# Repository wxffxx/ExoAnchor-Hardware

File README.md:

# ExoAnchor Hardware

[中文](README_zh.md)

This repository contains ExoAnchor hardware design outputs and hardware-specific instructions. Firmware, system architecture, and board capability truth live in the main [ExoAnchor repository](https://github.com/wxffxx/ExoAnchor).

## Current contents

| Path | Role |
| --- | --- |
| [`ESP32P4/exoanchor-p4-v2.4a6/`](ESP32P4/exoanchor-p4-v2.4a6/) | Standalone JLCEDA and KiCad V2.4A6 projects; conversion checked, manufacturing signoff pending |
| [`ESP32P4/exoanchor-p4-v2.3b4/`](ESP32P4/exoanchor-p4-v2.3b4/) | Standalone four-layer V2.3B4 JLCEDA and KiCad projects; historical revision, conversion checked |
| [`ESP32P4/exoanchor-p4-v2.3b6/`](ESP32P4/exoanchor-p4-v2.3b6/) | Standalone six-layer V2.3B6 JLCEDA and KiCad projects; historical revision, conversion checked |
| [`ESP32P4/simple-diy/`](ESP32P4/simple-diy/) | Waveshare simple DIY designs and expansion board |
| [`ESP32P4/archive/`](ESP32P4/archive/) | Historical material no longer used by new designs |
| `assets/brand/` | Brand geometry for PCB silkscreen |
| `ArmLinux/CM4_CH552/`, `ESP32S31/` | Reserved platform directories, not delivered designs |

A directory, netlist, or production output does not imply validated or production-ready hardware. A capability requires an identified revision, firmware profile, and corresponding hardware evidence.

Chinese documentation is authoritative. English README files are synchronized
mirrors; resolve differences from `_zh.md`.

## License

Original ExoAnchor software, firmware and documentation are licensed under the
[MIT License](LICENSE). Original hardware designs use the same policy, including
permission to manufacture and sell hardware from covered design files.

Unless a file says otherwise, this license covers all original materials that
the ExoAnchor contributors have the right to license, including schematics,
PCB and CAD source projects, BOMs, netlists, mechanical models, manufacturing
materials, and project documentation. Copies or substantial portions must
retain the copyright and permission notice from `LICENSE`. Third-party products
and materials retain their own terms; the MIT License does not grant rights to
ExoAnchor trademarks or third-party material.

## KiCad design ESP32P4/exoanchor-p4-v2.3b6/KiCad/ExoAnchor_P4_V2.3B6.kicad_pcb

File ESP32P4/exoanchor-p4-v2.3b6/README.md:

# ExoAnchor P4 V2.3B6 standalone project

[中文](README_zh.md)

Prepared on 2026-10-22 from local archives. This directory extracts `ESP32P4_Prototype_V2.3b6layers_260724封存` with its schematics, PCB, and library dependencies. No current cloud-project synchronization was performed. Chinese documentation is authoritative.

The native source marks `Appendix` as deleted. Only eight active design pages are included. The original repository netlist dated 2026-07-26 is also retained under `reference/` for historical traceability, not as a newly generated manufacturing output.

## Open the projects

| Format | Entry point | Instructions |
| --- | --- | --- |
| Native JLCEDA archive | [ExoAnchor_P4_V2.3B6.epro2](JLCEDA/ExoAnchor_P4_V2.3B6.epro2) | Successfully imported and PCB opened in fully offline JLCEDA Pro V4.1.60 |
| Native JLCEDA folder project | [ExoAnchor_P4_V2.3B6.eprj3](JLCEDA/ExoAnchor_P4_V2.3B6/ExoAnchor_P4_V2.3B6.eprj3) | Generated by the native application; keep its `pcb/` and `sch/` directories |
| KiCad project | [ExoAnchor_P4_V2.3B6.kicad_pro](KiCad/ExoAnchor_P4_V2.3B6.kicad_pro) | Keep the complete `KiCad/` directory |
| KiCad schematic | [ExoAnchor_P4_V2.3B6.kicad_sch](KiCad/ExoAnchor_P4_V2.3B6.kicad_sch) | Navigation root and eight design sheets |
| KiCad PCB | [ExoAnchor_P4_V2.3B6.kicad_pcb](KiCad/ExoAnchor_P4_V2.3B6.kicad_pcb) | 6 copper layers with tracks, vias, and copper zones |

Conversion and checks used **KiCad Nightly 10.99.0-1556-g74ef325b2f**. Compatibility with stable KiCad 9/10 was not verified. Local symbols, 38 footprints, and `${KIPRJMOD}` library tables are included. Relocating only `KiCad/` to an unrelated temporary directory produced an identical fresh netlist. Source 3D references are retained, but STEP/WRL geometry is not bundled.

## Checks and repairs

| Item | Result |
| --- | --- |
| Design | One board; eight active sheets plus the KiCad navigation root |
| Sheets | P1, USB_UART/Other IO, ETH, P4, HDMI_Captrue_MS2109, Power, PCIe, TF |
| Components | 185 in source PCB, KiCad PCB, and schematic; identical reference sets |
| Pads | 753 checked; pad-number sets and net names match |
| Connectivity | 149 / 149 nonempty source net endpoint sets match |
| Placement | No component position difference above 1 micrometre after import translation |
| PCB | 6 copper layers, 1841 straight tracks, 25 arc tracks, 401 vias |
| Free pads | Five extra footprint containers; 190 footprint objects in total |
| Native extraction | 220 design/library/support documents retain source bytes; configuration changes the default PCB |

Reports: [conversion parity](validation/parity.json), [native verification](validation/native-source-verification.json), [native application check](validation/native-open.json), [relocation](validation/portability.json).

The KiCad conversion repairs SMD pads, 185 schematic/PCB component links, cross-sheet labels, source short-circuit symbols, power references, and local library defaults. It restores 16 independent native PCIe wire groups to correct V2 compatibility-export merging of GND, 3V3AUX, and WAKE#. `U12.B10` is 3V3AUX; `U12.B11` is WAKE#. Front/back R-shaped copper artwork is reconstructed from source paths with arcs sampled at a maximum step of 2 degrees. Source text, frames, and layouts remain, including existing frame overlaps.

All nonzero native V3 straight tracks have matching V2 compatibility-export records. Both variants omit four zero-length native line records. See [track comparison](validation/native-track-comparison.json). Cross-format geometry is not claimed to be byte-identical. Native JLCEDA design documents are unchanged.

## Outstanding signoff

This is an extraction and conversion delivery, not manufacturing approval.

- KiCad DRC: **1521 items**, comprising 1329 errors and 192 warnings; zero reported unconnected items, no reported `shorting_items` or `invalid_padstack`. Clearance, track/via dimensions, thermals, board edges, silkscreen, and other findings remain.
- KiCad ERC: **777 items**, including pin conflicts, undriven pins, library differences, and dangling endpoints. Rules were not disabled or waived to clear the reports.
- These checks use default/imported KiCad rules. Original JLCEDA rules and manufacturing stackup parameters have not been exhaustively mapped; findings need attribution to source design, rule differences, or residual conversion differences.
- Native JLCEDA ERC/DRC, fabrication, assembly, power-on, and interface testing were not performed here.

See [rules summary](validation/rules-summary.json), [DRC](validation/pcb-drc.json), and [ERC](validation/sch-erc.json).

## Contents and provenance

| Path | Contents |
| --- | --- |
| `JLCEDA/` | Native import archive and editable folder project |
| `KiCad/` | Project, schematics, PCB, local symbols and footprints |
| `preview/` | PCB SVG/PNG, schematic SVG pages and overview; browsing aids |
| `reference/` | Original V2 compatibility export with known PCIe issue and historical 2026-07-26 netlist |
| `validation/` | Provenance, hashes, conversion repairs, connectivity and rule reports |
| `scripts/` | Standalone conversion verification scripts |
| `SHA256SUMS.txt` | Delivered file hashes |

Native source: `hardware-reserve/lceda-2026-10-01/source/ProPrj_ExoAnchor-ESP32P4_2026-09-30.epro2`. Initial KiCad import source: `ProPrj_ExoAnchor-ESP32P4_2026-10-19.epro`, followed by native-evidence repairs. Source hashes and extraction scope are in `validation/extraction-v3.json` and `validation/extraction.json`. These paths are provenance only; the original workspace is not required to open this delivery.

**Do not use `reference/V2_compatibility_export_as_received.epro` as the current design entry point.** Use the native `.epro2` or `.eprj3` above. `LICENSE` is copied from the hardware repository's MIT license; third-party library identifiers and properties remain.

## Repeat the checks

From this directory with a compatible `kicad-cli`:

```sh
kicad-cli sch export netlist --format kicadxml -o validation/kicad-netlist.xml KiCad/ExoAnchor_P4_V2.3B6.kicad_sch
python3 scripts/verify_conversion.py
```

The script resolves its own project directory and exits nonzero on parity failure. It does not replace ERC/DRC, manufacturing review, or physical validation.

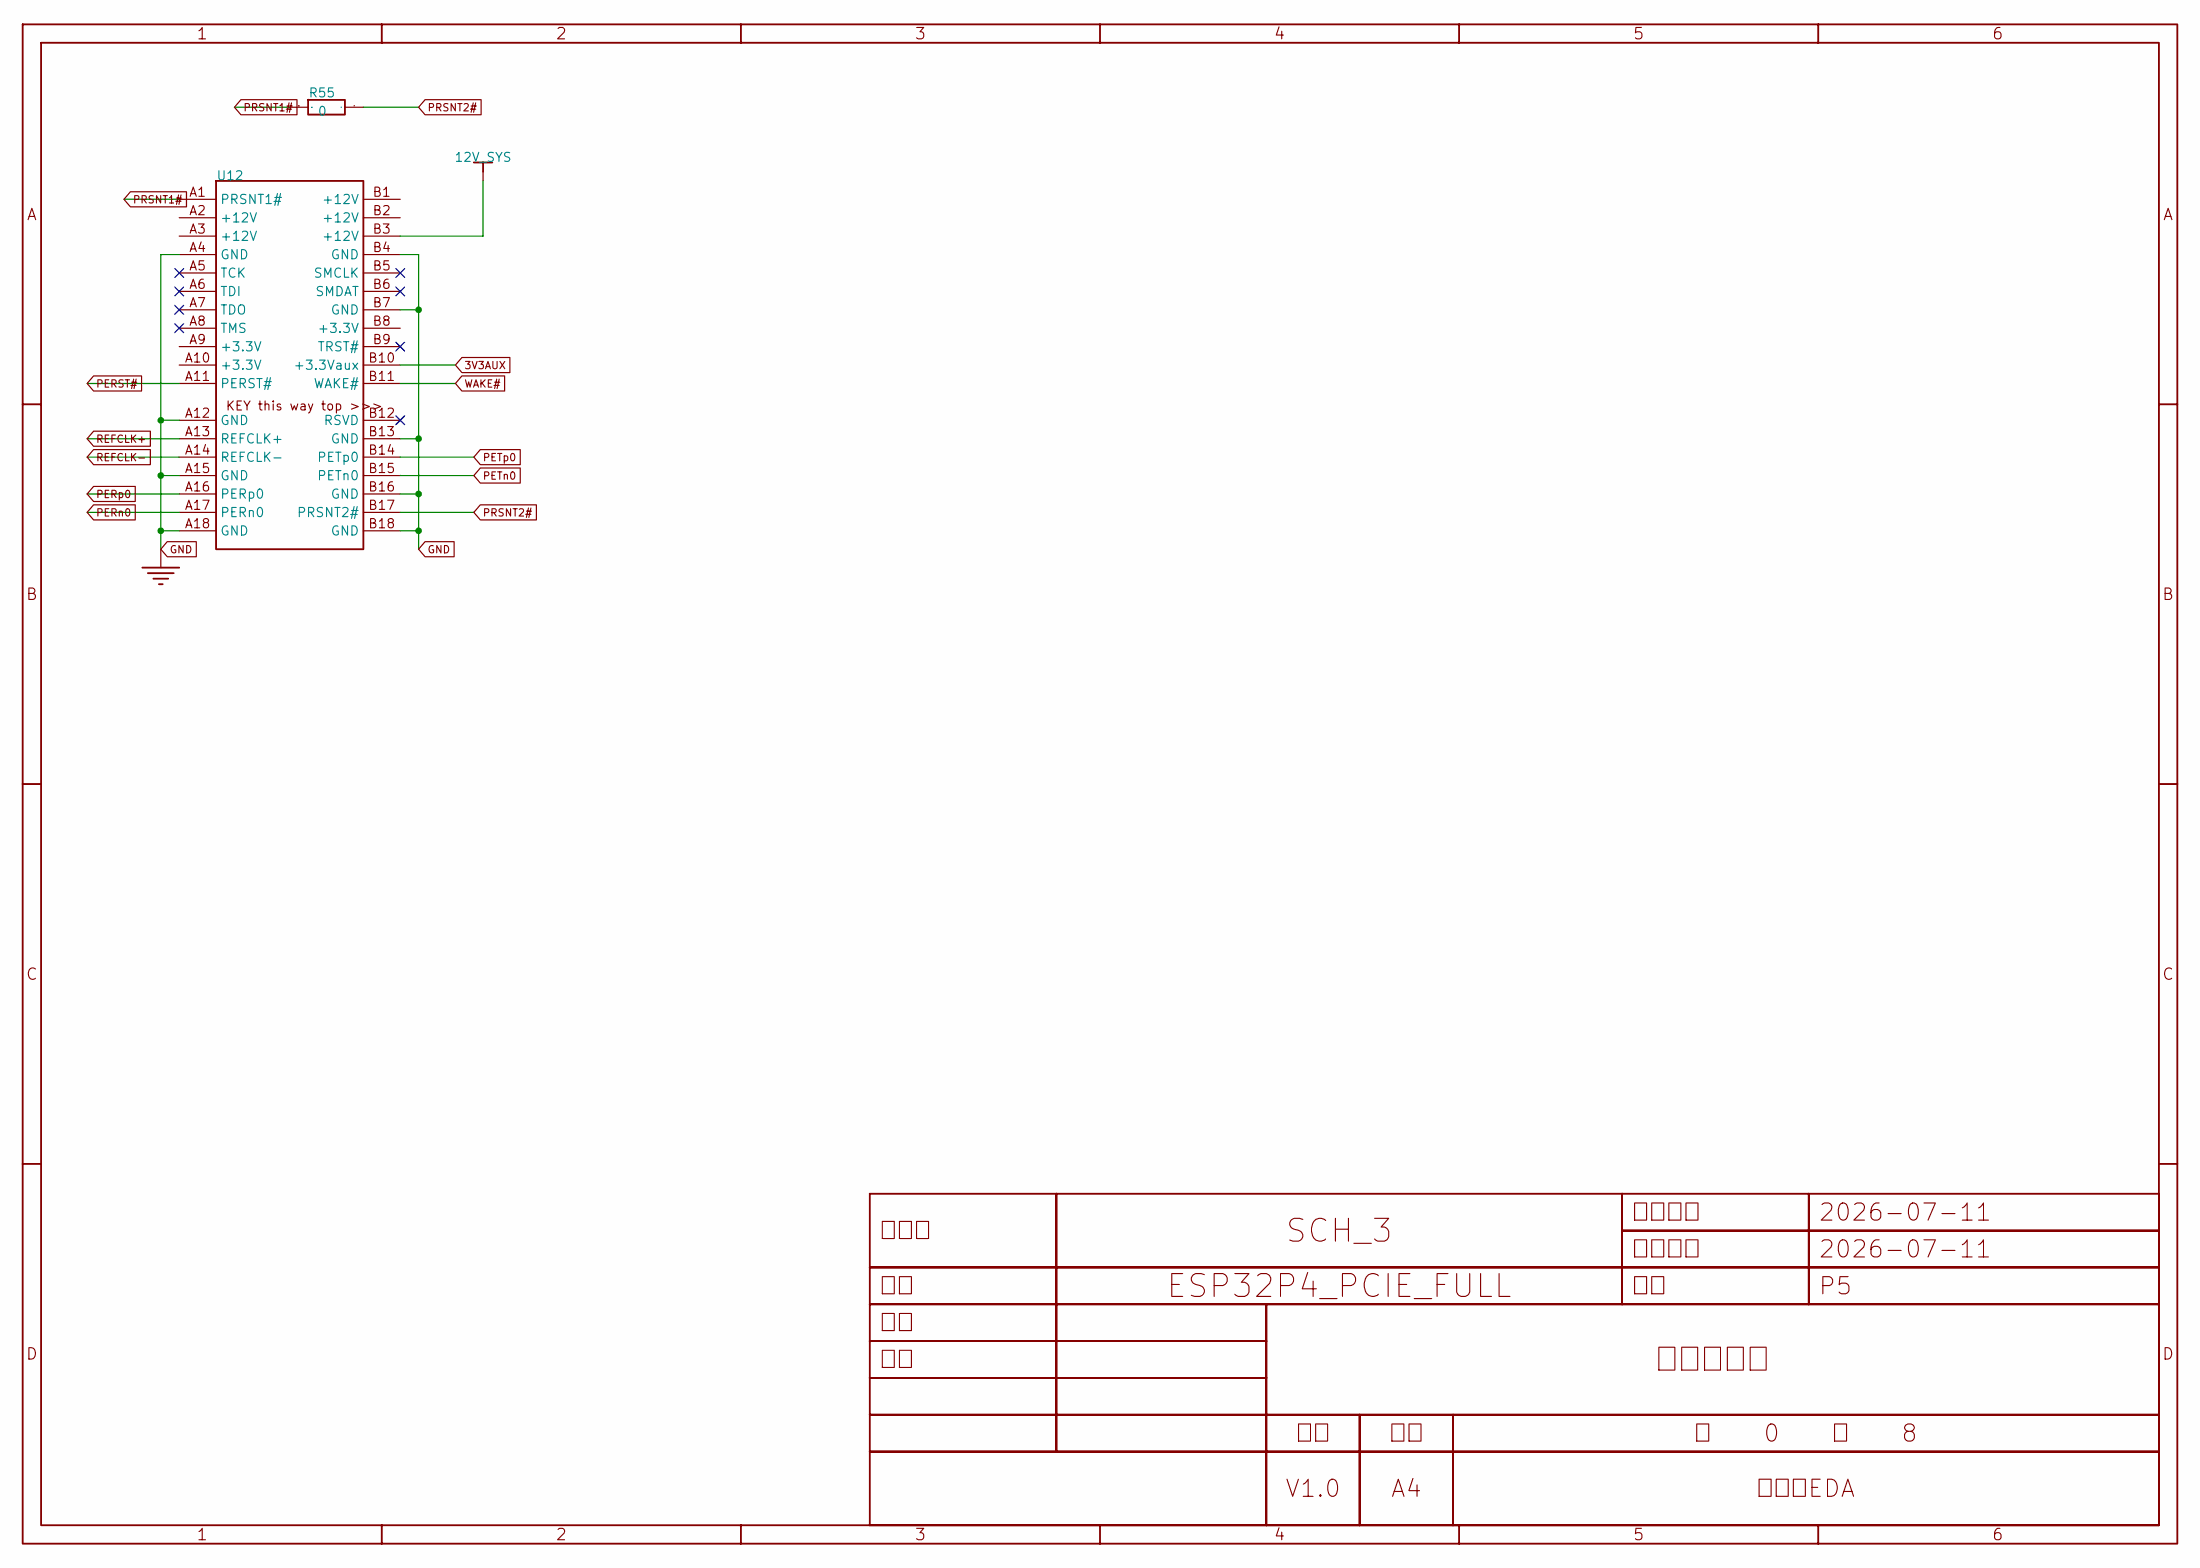
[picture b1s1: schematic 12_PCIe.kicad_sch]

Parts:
R55: 0; R0603__0f1821c5
U12: PCIe_1 key__ebaa1119

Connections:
3V3AUX: U12.B10 (+3.3Vaux); also elsewhere on the board
12V_SYS: U12.B3 (+12V); also elsewhere on the board
GND: U12.A4 (GND), U12.A12 (GND), U12.A15 (GND), U12.A18 (GND), U12.B4 (GND), U12.B7 (GND), U12.B13 (GND), U12.B16 (GND), U12.B18 (GND); also elsewhere on the board
PERN0: U12.A17 (PERn0)
PERP0: U12.A16 (PERp0)
PERST#: U12.A11 (PERST#)
PETN0: U12.B15 (PETn0)
PETP0: U12.B14 (PETp0)
PRSNT1#: R55.1, U12.A1 (PRSNT1#)
PRSNT2#: R55.2, U12.B17 (PRSNT2#)
REFCLK+: U12.A13 (REFCLK+)
REFCLK-: U12.A14 (REFCLK-)
WAKE#: U12.B11 (WAKE#)

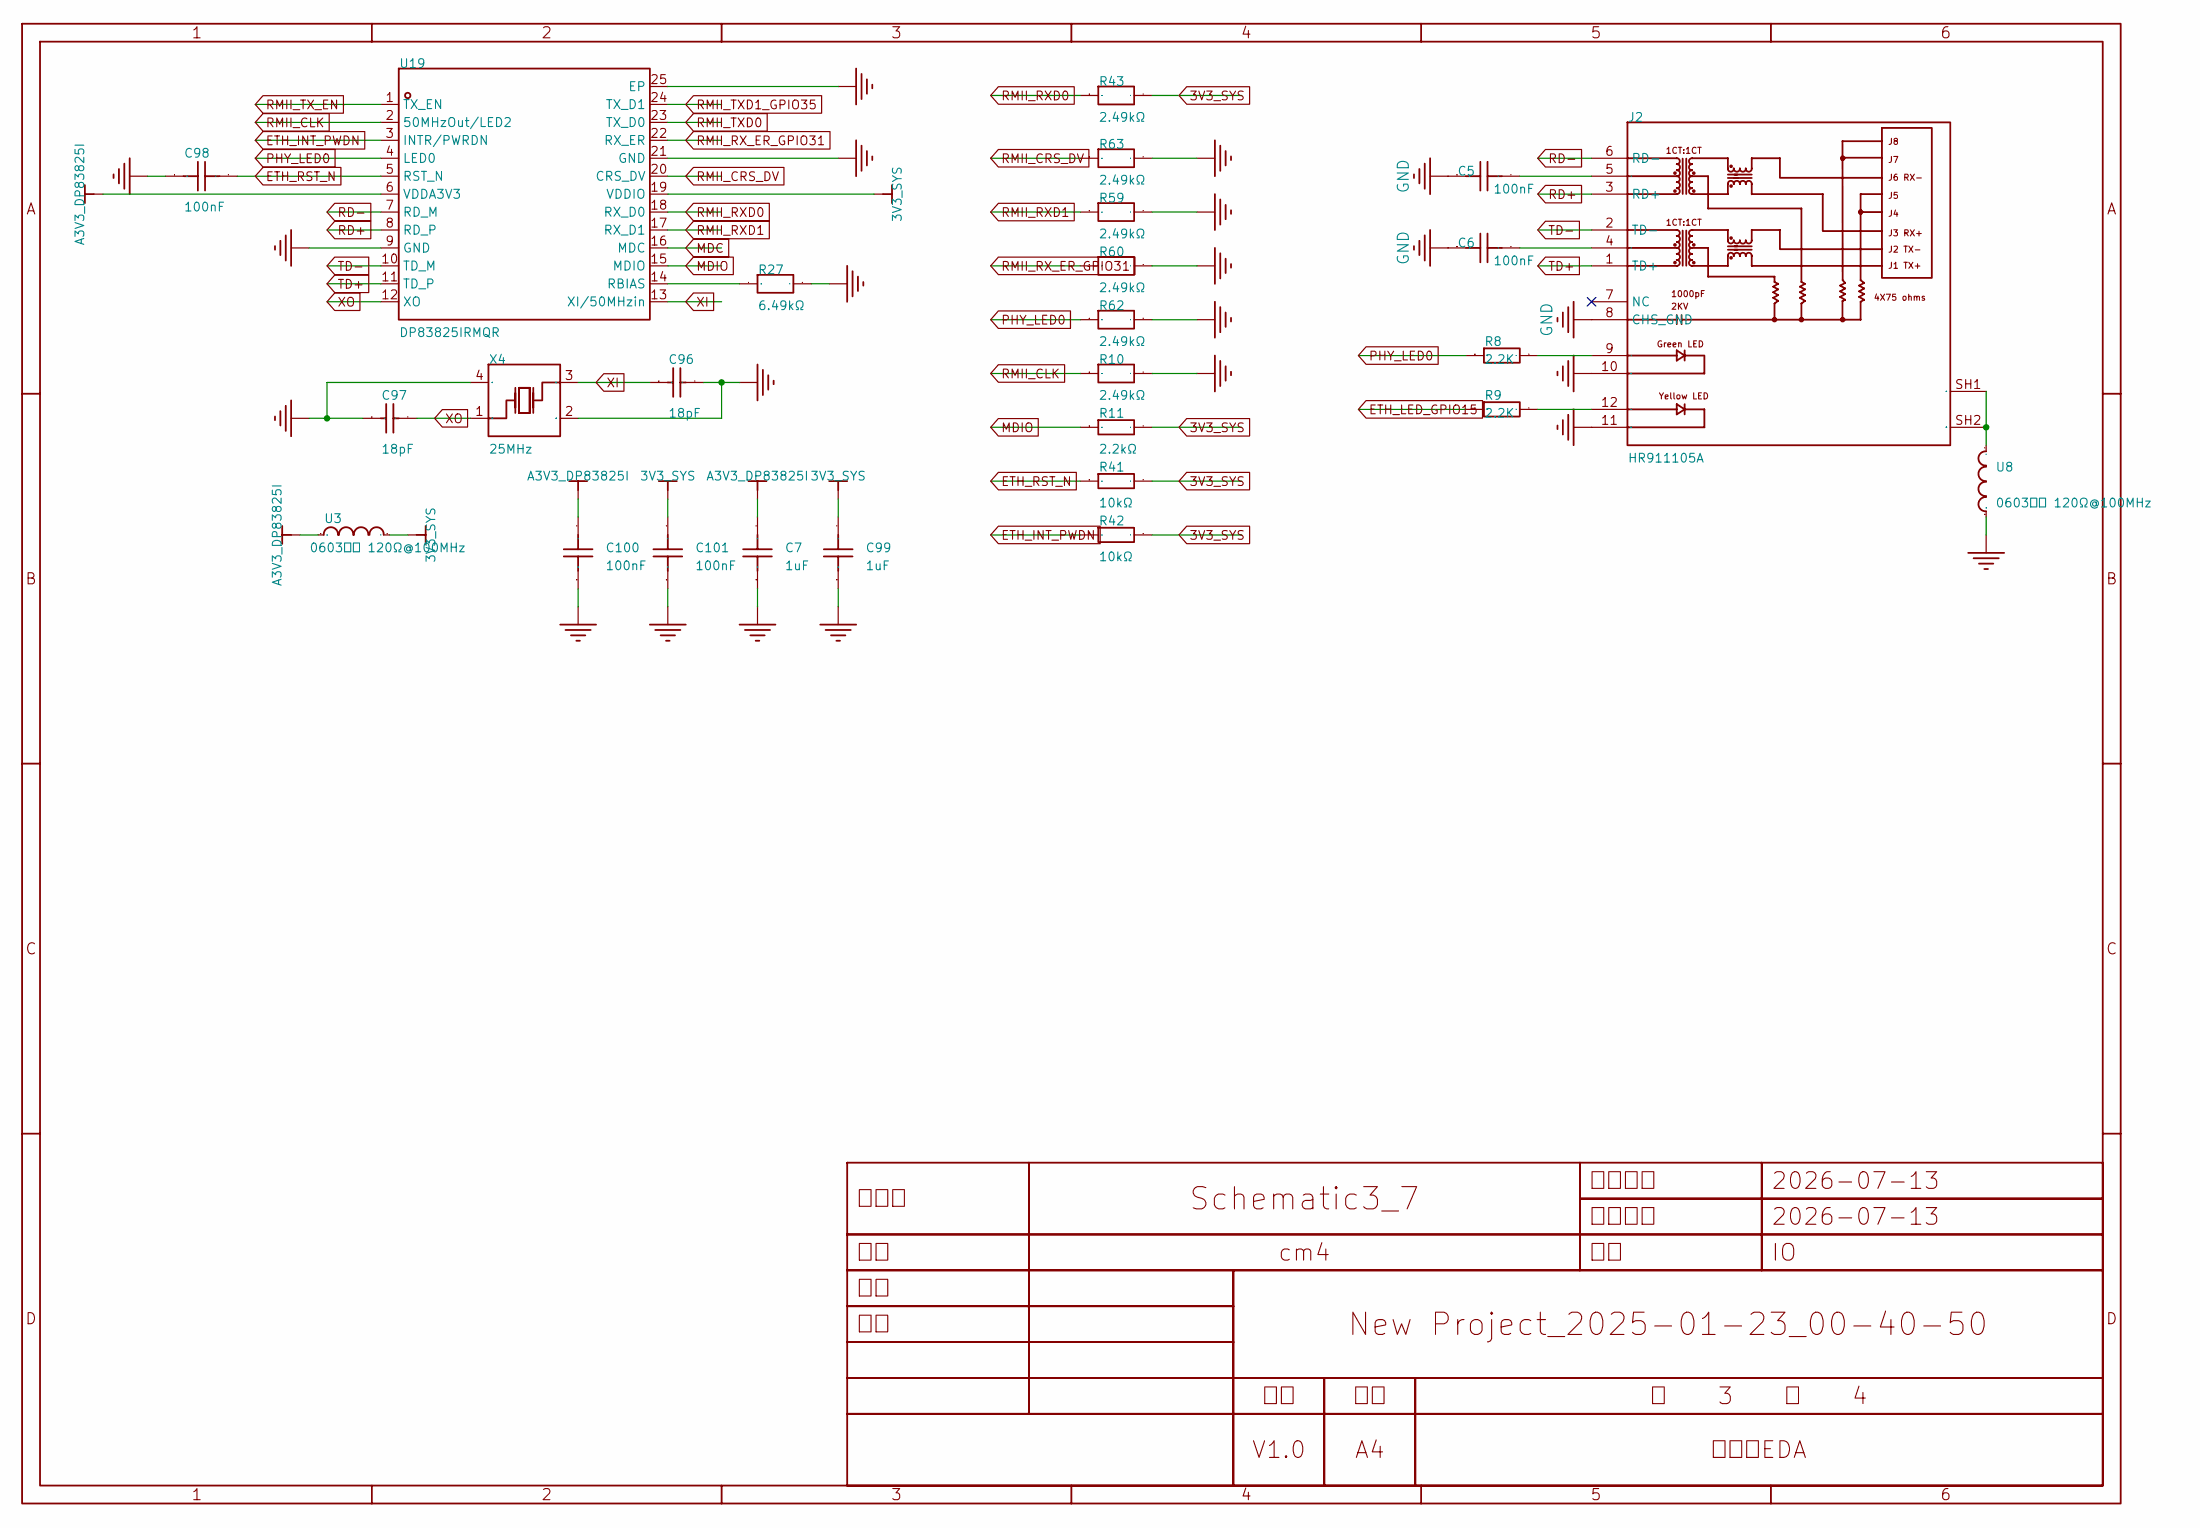
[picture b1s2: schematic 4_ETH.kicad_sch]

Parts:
C5, C6, C98, C100, C101: 100nF; C0402 去耦电容__92f207f8; Tolerance ±10%; Voltage Rated 50V; Manufacturer Part CC0603KRX7R9BB104; LCSC Part Name 100nF ±10% 50V
C7, C99: 1uF; C0603__a4480e4e; Tolerance ±10%; Voltage Rating 25V; Manufacturer Part CL05A105KA5NQNC; LCSC Part Name 1uF ±10% 25V
C96, C97: 18pF; C0402__aba8f707; Tolerance ±5%; Voltage Rating 50V; Manufacturer Part CL10C180JB8NNNC; LCSC Part Name 18pF ±5% 50V
J2: HR911105A; RJ45-TH_HR911105A__b23e0a26; Manufacturer Part HR911105A; LCSC Part Name 弯插 带LED
R8, R9: 2.2K; R0402__b4a31b25; Tolerance ±1%; Voltage-Supply(Max) 50V; Manufacturer Part FRC0402F5100TS; LCSC Part Name 510Ω ±1% 62.5mW 厚膜电阻
R10, R43, R59, R60, R62, R63: 2.49kΩ; R0402__b4a31b25; Tolerance ±0.1%; Voltage-Supply(Max) 75V; Manufacturer Part RT0603BRE072K49L; LCSC Part Name 薄膜电阻 2.49kΩ ±0.1% 100mW
R11: 2.2kΩ; R0402__b4a31b25; Overload Voltage (Max) 75V; Tolerance ±1%; Manufacturer Part 0603WAF2201T5E; LCSC Part Name 2.2kΩ ±1% 100mW 厚膜电阻
R27: 6.49kΩ; R0402__b4a31b25; Tolerance ±1%; Voltage-Supply(Max) 75V; Manufacturer Part FRC0603F6491TS; LCSC Part Name 6.49kΩ ±1% 100mW 厚膜电阻
R41, R42: 10kΩ; R0402__b4a31b25; Tolerance ±1%; Voltage-Supply(Max) 75V; Manufacturer Part 0603WAF1002T5E; LCSC Part Name 厚膜电阻 10kΩ ±1% 100mW
U3, U8: BLM18PG121SN1D; L0603__0fd5099d; Current Rating 2A; Tolerance ±25%; Manufacturer Part BLM18PG121SN1D; LCSC Part Name 0603磁珠 120Ω@100MHz
U19: DP83825IRMQR; HVQFN-24_L3.0-W3.0-P0.40-TL-EP1.9__a0141fe0; Voltage - Supply 1.8V；3.3V; Manufacturer Part DP83825IRMQR; LCSC Part Name DP83825I低功耗10/100Mbps以太网物理层收发器
X4: 25MHz; CRYSTAL-SMD_4P-L3.2-W2.5-BL__9c9dbee8; Manufacturer Part X322525MOB4SI; LCSC Part Name YSX321SL 25MHZ 4P 3225 12PF ±10PPM -40~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

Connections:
3V3_SYS: C99.2, C101.2, R11.2, R41.2, R42.2, R43.2, U3.2, U19.19 (VDDIO); also elsewhere on the board
$4N12777: R27.1, U19.14 (RBIAS)
$4N12791: J2.SH1, J2.SH2, U8.2
$4N12794: J2.12, R9.2
$4N12797: J2.9, R8.2
$4N12802: C6.2, J2.4
$4N12803: C5.2, J2.5
A3V3_DP83825I: C7.2, C100.2, U3.1, U19.6 (VDDA3V3)
ETH_INT_PWDN: R42.1, U19.3 (INTR/PWRDN); also elsewhere on the board
ETH_LED_GPIO15: R9.1; also elsewhere on the board
ETH_RST_N: C98.2, R41.1, U19.5 (RST_N); also elsewhere on the board
GND: C5.1, C6.1, C7.1, C96.2, C97.1, C98.1, C99.1, C100.1, C101.1, J2.8 (CHS_GND), J2.10, J2.11, R10.2, R27.2, R59.2, R60.2, R62.2, R63.2, U8.1, U19.9 (GND), U19.21 (GND), U19.25 (EP), X4.2 (GND), X4.4 (GND); also elsewhere on the board
MDC: U19.16 (MDC); also elsewhere on the board
MDIO: R11.1, U19.15 (MDIO); also elsewhere on the board
PHY_LED0: R8.1, R62.1, U19.4 (LED0)
RD+: J2.3 (RD+), U19.8 (RD_P)
RD-: J2.6 (RD-), U19.7 (RD_M)
RMII_CLK: R10.1, U19.2 (50MHzOut/LED2); also elsewhere on the board
RMII_CRS_DV: R63.1, U19.20 (CRS_DV); also elsewhere on the board
RMII_RXD0: R43.1, U19.18 (RX_D0); also elsewhere on the board
RMII_RXD1: R59.1, U19.17 (RX_D1); also elsewhere on the board
RMII_RX_ER_GPIO31: R60.1, U19.22 (RX_ER); also elsewhere on the board
RMII_TXD0: U19.23 (TX_D0); also elsewhere on the board
RMII_TXD1_GPIO35: U19.24 (TX_D1); also elsewhere on the board
RMII_TX_EN: U19.1 (TX_EN); also elsewhere on the board
TD+: J2.1 (TD+), U19.11 (TD_P)
TD-: J2.2 (TD-), U19.10 (TD_M)
XI: C96.1, U19.13 (XI/50MHzin), X4.3 (OSC2)
XO: C97.2, U19.12 (XO), X4.1 (OSC1)

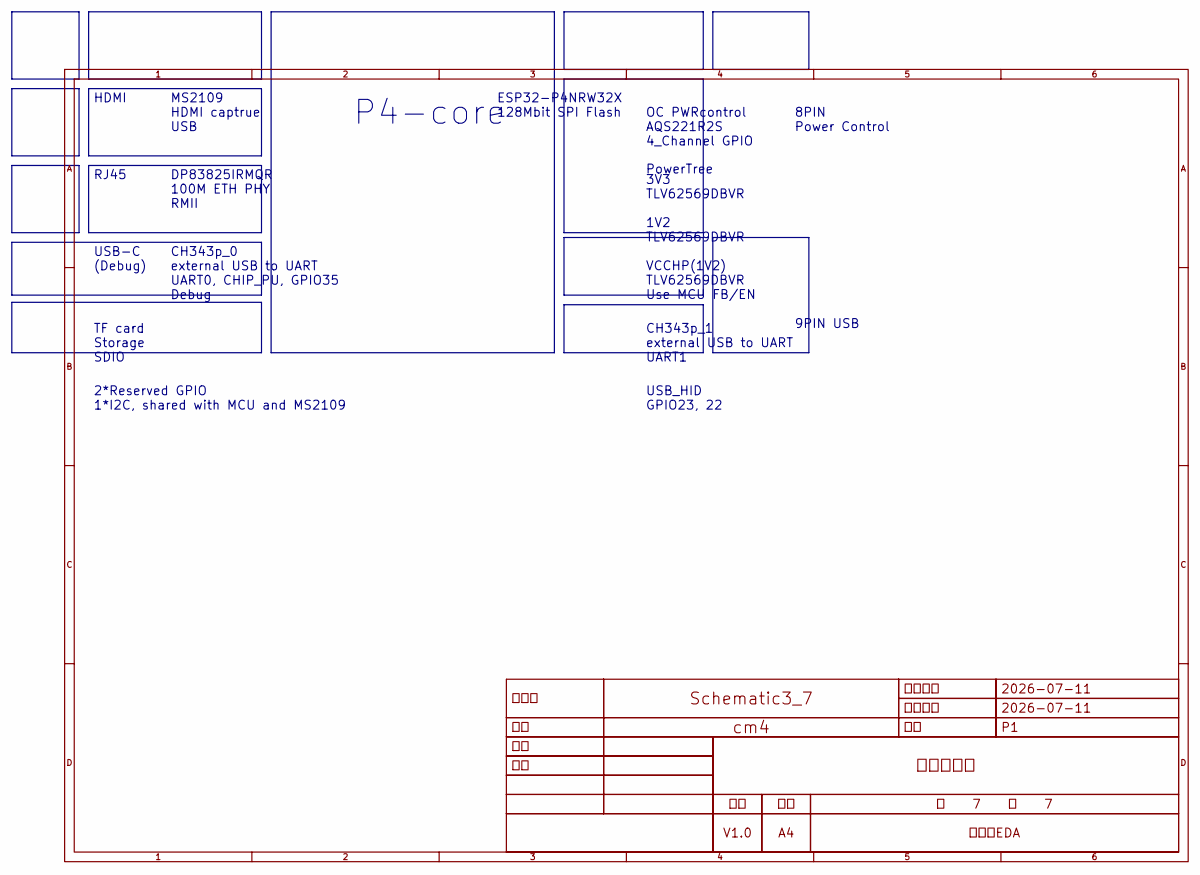
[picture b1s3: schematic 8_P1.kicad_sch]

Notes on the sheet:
MS2109 HDMI captrue USB
RJ45
DP83825IRMQR 100M ETH PHY RMII
USB_HID GPIO23, 22
CH343p_0 external USB to UART UART0, CHIP_PU, GPIO35 Debug
2*Reserved GPIO 1*I2C, shared with MCU and MS2109
HDMI
3V3 TLV62569DBVR 1V2 TLV62569DBVR VCCHP(1V2) TLV62569DBVR Use MCU FB/EN
USB-C (Debug)
OC PWRcontrol AQS221R2S 4_Channel GPIO
CH343p_1 external USB to UART UART1
P4-core
PowerTree
9PIN USB
8PIN Power Control
ESP32-P4NRW32X 128Mbit SPI Flash
TF card Storage SDIO

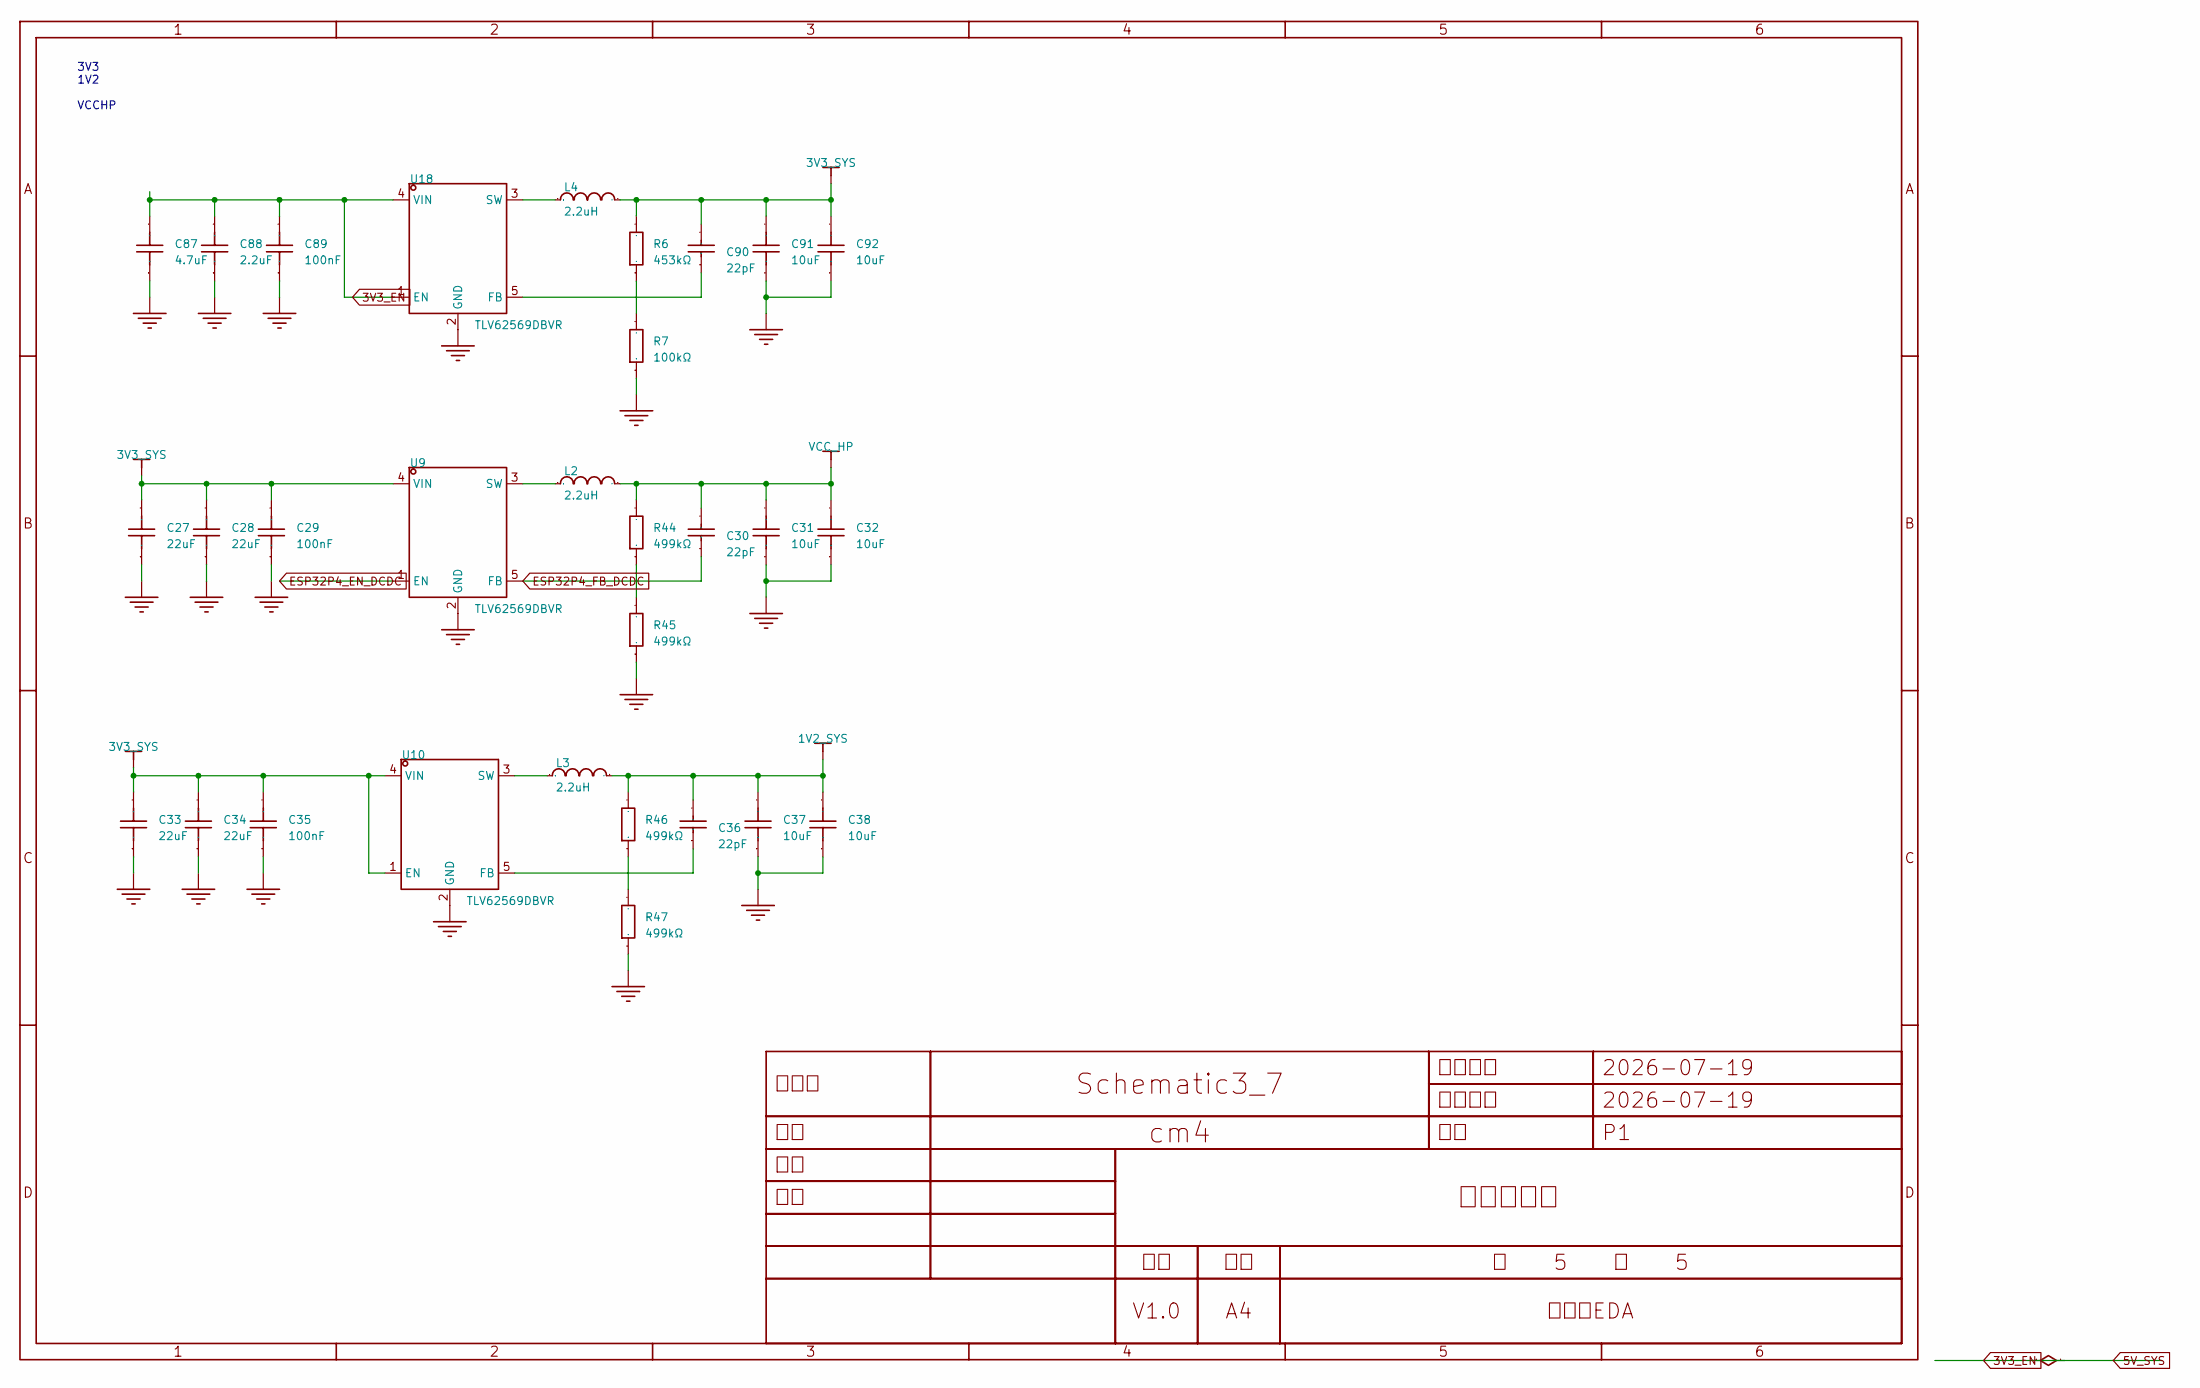
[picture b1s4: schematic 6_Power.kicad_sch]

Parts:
C27, C28, C33, C34: 22uF; C0805__eb27e37a; Tolerance ±20%; Voltage Rating 25V; Manufacturer Part CL21A226MAQNNNE; LCSC Part Name 22uF ±20% 25V
C29, C35, C89: 100nF; C0603__a4480e4e; Tolerance ±10%; Voltage Rating 50V; Manufacturer Part CL10B104KB8NNNC; LCSC Part Name 100nF ±10% 50V
C30, C36: 22pF; C0603__a4480e4e; Tolerance ±5%; Voltage Rating 50V; Manufacturer Part CL10C220JB8NNNC; LCSC Part Name 22pF ±5% 50V
C31, C32, C37, C38: 10uF; C0805__eb27e37a; Tolerance ±10%; Voltage Rating 25V; Manufacturer Part CL21A106KAYNNNE; LCSC Part Name 10uF ±10% 25V
C87: 4.7uF; C0805__eb27e37a; Tolerance ±20%; Voltage Rated 25V; Manufacturer Part CL21A226MAQNNNE; LCSC Part Name 22uF ±20% 25V
C88: 2.2uF; C0805__eb27e37a; Tolerance ±20%; Voltage Rated 25V; Manufacturer Part CL21A226MAQNNNE; LCSC Part Name 22uF ±20% 25V
C90: 22pF; C0603__a4480e4e; Tolerance ±5%; Voltage Rating 50V; Manufacturer Part CC0603JRNPO9BN121; LCSC Part Name 120pF ±5% 50V
C91, C92: 10uF; C0805__eb27e37a; Tolerance ±10%; Voltage Rated 25V; Manufacturer Part CL21A106KAYNNNE; LCSC Part Name 10uF ±10% 25V
L2, L3, L4: 2.2uH; IND-SMD_L3.0-W3.0_FNR30XXS__6930f09c; Current Rating 2A; Tolerance ±20%; Manufacturer Part FNR3015S2R2MT; LCSC Part Name 2.2uH ±20% 2A
R6: 453kΩ; R0603__0f1821c5; Tolerance ±1%; Voltage-Supply(Max) 75V; Manufacturer Part FRC0603F4533TS; LCSC Part Name 453kΩ ±1% 100mW 厚膜电阻
R7: 100kΩ; R0603__0f1821c5; Overload Voltage (Max) 75V; Tolerance ±1%; Manufacturer Part 0603WAF1003T5E; LCSC Part Name 100kΩ ±1% 100mW 厚膜电阻
R44, R45, R46, R47: 499kΩ; R0603__0f1821c5; Tolerance ±1%; Voltage-Supply(Max) 75V; Manufacturer Part FRC0603F4993TS; LCSC Part Name 499kΩ ±1% 100mW 厚膜电阻
U9, U10: TLV62569DBVR; SOT-23-5_L3.0-W1.7-P0.95-LS2.8-BR__f09f3096; Manufacturer Part TLV62569DBVR; LCSC Part Name 降压型 2A 2.5V~5.5V
U18: TLV62569DBVR; SOT-23-5_L3.0-W1.7-P0.95-LS2.8-BR__f09f3096; Output Voltage 600mV~5.5V; Voltage - Supply 2.5V~5.5V; Manufacturer Part TLV62569DBVR; LCSC Part Name 降压型 2A 2.5V~5.5V

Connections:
1V2_SYS: C36.2, C37.2, C38.2, L3.2, R46.2; also elsewhere on the board
3V3_SYS: C27.2, C28.2, C29.2, C33.2, C34.2, C35.2, C90.2, C91.2, C92.2, L4.2, R6.2, U9.4 (VIN), U10.1 (EN), U10.4 (VIN); also elsewhere on the board
$6N47: L2.1, U9.3 (SW)
$6N67: L3.1, U10.3 (SW)
$6N72: C36.1, R46.1, R47.2, U10.5 (FB)
$6N85: L4.1, U18.3 (SW)
$6N90: C90.1, R6.1, R7.2, U18.5 (FB)
ESP32P4_EN_DCDC: U9.1 (EN); also elsewhere on the board
ESP32P4_FB_DCDC: C30.1, R44.1, R45.2, U9.5 (FB); also elsewhere on the board
GND: C27.1, C28.1, C29.1, C31.1, C32.1, C33.1, C34.1, C35.1, C37.1, C38.1, C87.1, C88.1, C89.1, C91.1, C92.1, R7.1, R45.1, R47.1, U9.2 (GND), U10.2 (GND), U18.2 (GND); also elsewhere on the board
VCC_HP: C30.2, C31.2, C32.2, L2.2, R44.2; also elsewhere on the board

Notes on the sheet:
3V3 1V2 VCCHP
